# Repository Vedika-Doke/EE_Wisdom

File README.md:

# EE_Wisdom

**Engineering Projects & Research Repository**

Academic projects, hands-on engineering work, and interactive study tools spanning electrical engineering, embedded systems, digital design, and hardware development — built over multiple roles and coursework at IIT Bombay.

Each project lives in its own folder on `main`. Interactive study guides are served via GitHub Pages from the [`EE_LearningAids`](https://github.com/Vedika-Doke/EE_Wisdom/tree/EE_LearningAids) branch.

---

## Repository Structure

| Folder / Branch | Contents |
|---|---|
| [`WISH/`](WISH/) | TI WiSH Hardware Summer School (2026) — digital Verilog labs, analog prework/quizzes, and a smart bus-tracking group project (server-side ETA engine) |
| [`EE301-EMWaves/`](EE301-EMWaves/) | EE301 (Electromagnetic Waves) — full transmission-lines explainer, ground-floor-up |
| [`EE309-Microprocessors-Project/`](EE309-Microprocessors-Project/) | AT89C5131A + MCP4921 DAC + MCP3008 ADC — sine wave generation, NCO, Goertzel tone detection |
| [`EE337-MicroLab-Project/`](EE337-MicroLab-Project/) | 8051 MicroLab project — I2C LCD interfacing and R2C driver |
| [`Electrical-trainee-racing-team/`](Electrical-trainee-racing-team/) | ECU firmware, AMS/BMS research, HV-LV isolation, and comms protocol work for a student electric racing team |
| [`JDE-Tenure/`](JDE-Tenure/) | Two complete KiCad PCB designs — STM32 dashboard board and a sensor testing board |
| [`ToyCPU-1281/`](ToyCPU-1281/) | VHDL-based 8-bit toy CPU (i281) with custom ISA and Bubble Sort implementation |
| [`EE_LearningAids`](https://github.com/Vedika-Doke/EE_Wisdom/tree/EE_LearningAids) (branch) | Interactive browser-based study guides — [live site](https://vedika-doke.github.io/EE_Wisdom/) |

---

## EE_LearningAids

Interactive, single-file HTML study tools — open directly in any browser, no setup or internet needed.

### IIT Bombay Course Guides

#### EE238 — Power Engineering II
- 10 topic modules: transmission lines, 3-phase systems, per-unit analysis, ABCD parameters, P & Q flow, Maxwell's equations
- 18+ MCQs with click-to-reveal solutions
- 6 long-form worked problems (Review Q 5A style) with step-by-step strategies
- Textbook examples from Weedy Ch 2–3, master formula sheet
- Dark theme, mobile-friendly, works offline

#### EE309 — Microprocessors & Computer Architecture
- Full 8051 coverage: Von Neumann vs Harvard, memory map (ROM/RAM/SFR), internal RAM breakdown
- Registers, PSW flags, 5 addressing modes, instruction set (arithmetic, logical, jump, bit-level)
- Timers, interrupts (IE/IP registers, interrupt priority), serial communication (SCON, SBUF, baud rate)
- Machine cycles, timing diagrams, and common exam traps

### Aptitude & Test Prep (TI WiSH 2025)

#### `wish_prep.html` — TI WiSH Interactive Quiz
- Sections: Past Year Questions (WiSH 2024), Mathematics, Basic Electronics, Programming (tricky C)
- Full Mixed Mock Test mode (timed, randomized)
- Click-to-reveal explanations with worked solutions
- Covers: LTI systems, ROC, op-amps (CMRR, slew rate, virtual ground), MOSFET regions, CMOS, Boolean algebra, pointer arithmetic, short overflow, recursion output

#### `math_aptitude_mcq.html` — Advanced Math Bank
- 20 questions: Bayes' Theorem, Derangements, Pigeonhole Principle, Inclusion-Exclusion, Modular Arithmetic, Eigenvalues, Geometric Probability

#### `theory_revision.html` — Theory Revision Sheet
- **Probability:** Addition/Multiplication/Bayes rules, nPr/nCr, circular permutations, Stars & Bars, distributions (Binomial, Geometric, Poisson, Uniform), Expected Value, Variance, Derangements
- **Profit & Loss:** CP/SP/Profit%/Loss%, Mark-up + Discount formula, successive discounts, dishonest dealer, "sell x for cost of y" — with fraction↔percentage cheatsheet
- **C++ FAQs:** Data types & overflow, pointer arithmetic traps, operator precedence, bitwise tricks, storage classes, struct vs union vs class, virtual functions, time complexity table
- 45+ new interactive MCQs across all three topics with explanations

---

## Electrical-trainee-racing-team

Work done as an Electrical Trainee for a student FSAE electric racing team.

### `Comms/` — Controls, Communication & Data Acquisition

**ECU Firmware** (`Comms/Src/ECU/`) — C++ / PlatformIO
- FSAE rulebook-compliant ECU (Rules T11.8.x)
- CAN bus communication at 500 kbps; DBC file included for signal decoding
- APPS (Accelerator Pedal Position Sensor) plausibility check — 10% agreement threshold (T11.8.4)
- BPS (Brake Pressure Sensor) monitoring with hard-braking detection (T11.8.6)
- Torque command pipeline: APPS → scaled torque request → CAN frame to motor controller
- RFE acknowledgement sequencing, motor off-sequence with timed delays
- I2C/SPI/UART protocol implementations (PlatformIO project under `Comms/PlatformIO/`)

**Theory Notes** (`Comms/Theory/`)
- Serial vs parallel communication, simplex/half-duplex/full-duplex
- Deep dive into CAN, I2C, SPI, UART — framing, arbitration, addressing, error handling

### `AMS/` — Accumulator Management System

- BMS fundamentals: SOC (State of Charge), SOH (State of Health), SOE (State of Envelope)
- 96s5p Li-ion pack configuration (480 cells, max 403.2 V), stack architecture
- BMS protection: overvoltage, overcurrent, thermal cutoff
- `DataAnalysis.ipynb` — Python notebook for crude data analysis of accumulator telemetry
- PDF module notes: `AMS module '25.pdf`

### `HV_LV/` — High Voltage / Low Voltage Systems

- Galvanic isolation — theory and FSAE rulebook requirements (EV 1.2.1)
- Optocoupler interfacing (datasheet included)
- 555-timer theory notes
- ESI (Electronic System Integration) module notes — noise rejection, fault containment, ground loops

### `TheoryBits/` — Reference PDFs

Quick-reference theory sheets produced during the tenure:
- MOSFETs, Op-Amps & Phasors, Op-Amp 2.0, Buck Converter
- Communication Protocols, Digital Logic
- Team session notes (Racing Team April 4)

---

## JDE-Tenure

Two complete PCB designs, both fully designed in KiCad (schematic + layout + BOM + 3D model).

### `DASH_PCB_STM32/` — Dashboard PCB (STM32-based)

- STM32 microcontroller at the core
- Full KiCad project: schematic (`.kicad_sch`), PCB layout (`.kicad_pcb`), project file, net files, BOM (`.csv`), 3D model (`.step`)
- Multiple netlist iterations (`net.net` → `netfinal.net`) reflecting design revisions
- Design backups preserved (Nov 2025)

### `Sensor_testing_PCB/` — Sensor Testing Board

- Purpose-built board for validating sensor interfacing before integration
- Full KiCad project: schematic, PCB layout, BOM, net file
- Backup snapshots included (Sep 2025)

---

## ToyCPU-1281

Course project: design and implementation of an 8-bit toy CPU (i281).

- VHDL-based datapath and control unit
- Custom instruction set architecture (ISA)
- Bubble Sort implemented directly on memory data
- Functional simulation and verification

---

## WISH

TI **WiSH Hardware Mentee (2026)** — kept as an academic-help resource. See [`WISH/`](WISH/) for the full breakdown.

- **Week 1 — Digital Design:** two Verilog labs (shift-add and DFT-instrumented sequential multipliers) with testbenches, test plans, and simulation waveforms; prework guides and daily surveys
- **Week 2 — Analog:** prework, ASLKv2010 starter-kit reference, and topic quizzes (Fourier/Laplace, inductors, RC circuits)
- **Project — Smart Bus Tracking:** a rural bus tracking + ETA system with a runnable Python prediction engine (EWMA segment learning, dead reckoning, geofencing), full server-side math writeups, and design diagrams

---

## Tools & Technologies

| Category | Details |
|---|---|
| **Languages** | C++, Python, VHDL, HTML/JS |
| **Embedded** | PlatformIO, 8051, STM32, CAN bus |
| **PCB Design** | KiCad (schematic, layout, BOM, 3D) |
| **EDA / Simulation** | LTspice, Quartus, MATLAB/Simulink |
| **Protocols** | CAN (500 kbps), I2C, SPI, UART |
| **Domains** | Embedded systems, automotive electronics, digital design, power engineering, test prep tooling |

---

## EE309-Microprocessors-Project

Hardware project for EE309 (Microprocessors) — AT89C5131A microcontroller driving external DAC/ADC over SPI.

| Phase | Description |
|---|---|
| `phase1/` | Basic MCP4921 DAC sine wave output via lookup table |
| `phase2/` | NCO (Numerically Controlled Oscillator) — frequency-agile sine generation |
| `phase3/` | MCP3008 ADC integration — loopback DAC→ADC measurement |
| `phase3_goertzel/` | Goertzel algorithm for single-bin tone detection on ADC samples |
| `src/` | Latest working source files |

---

## Notes

- All HTML study tools are offline-capable — open in a browser or visit the [live site](https://vedika-doke.github.io/EE_Wisdom/).
- Study guides are served from the `EE_LearningAids` branch via GitHub Pages.

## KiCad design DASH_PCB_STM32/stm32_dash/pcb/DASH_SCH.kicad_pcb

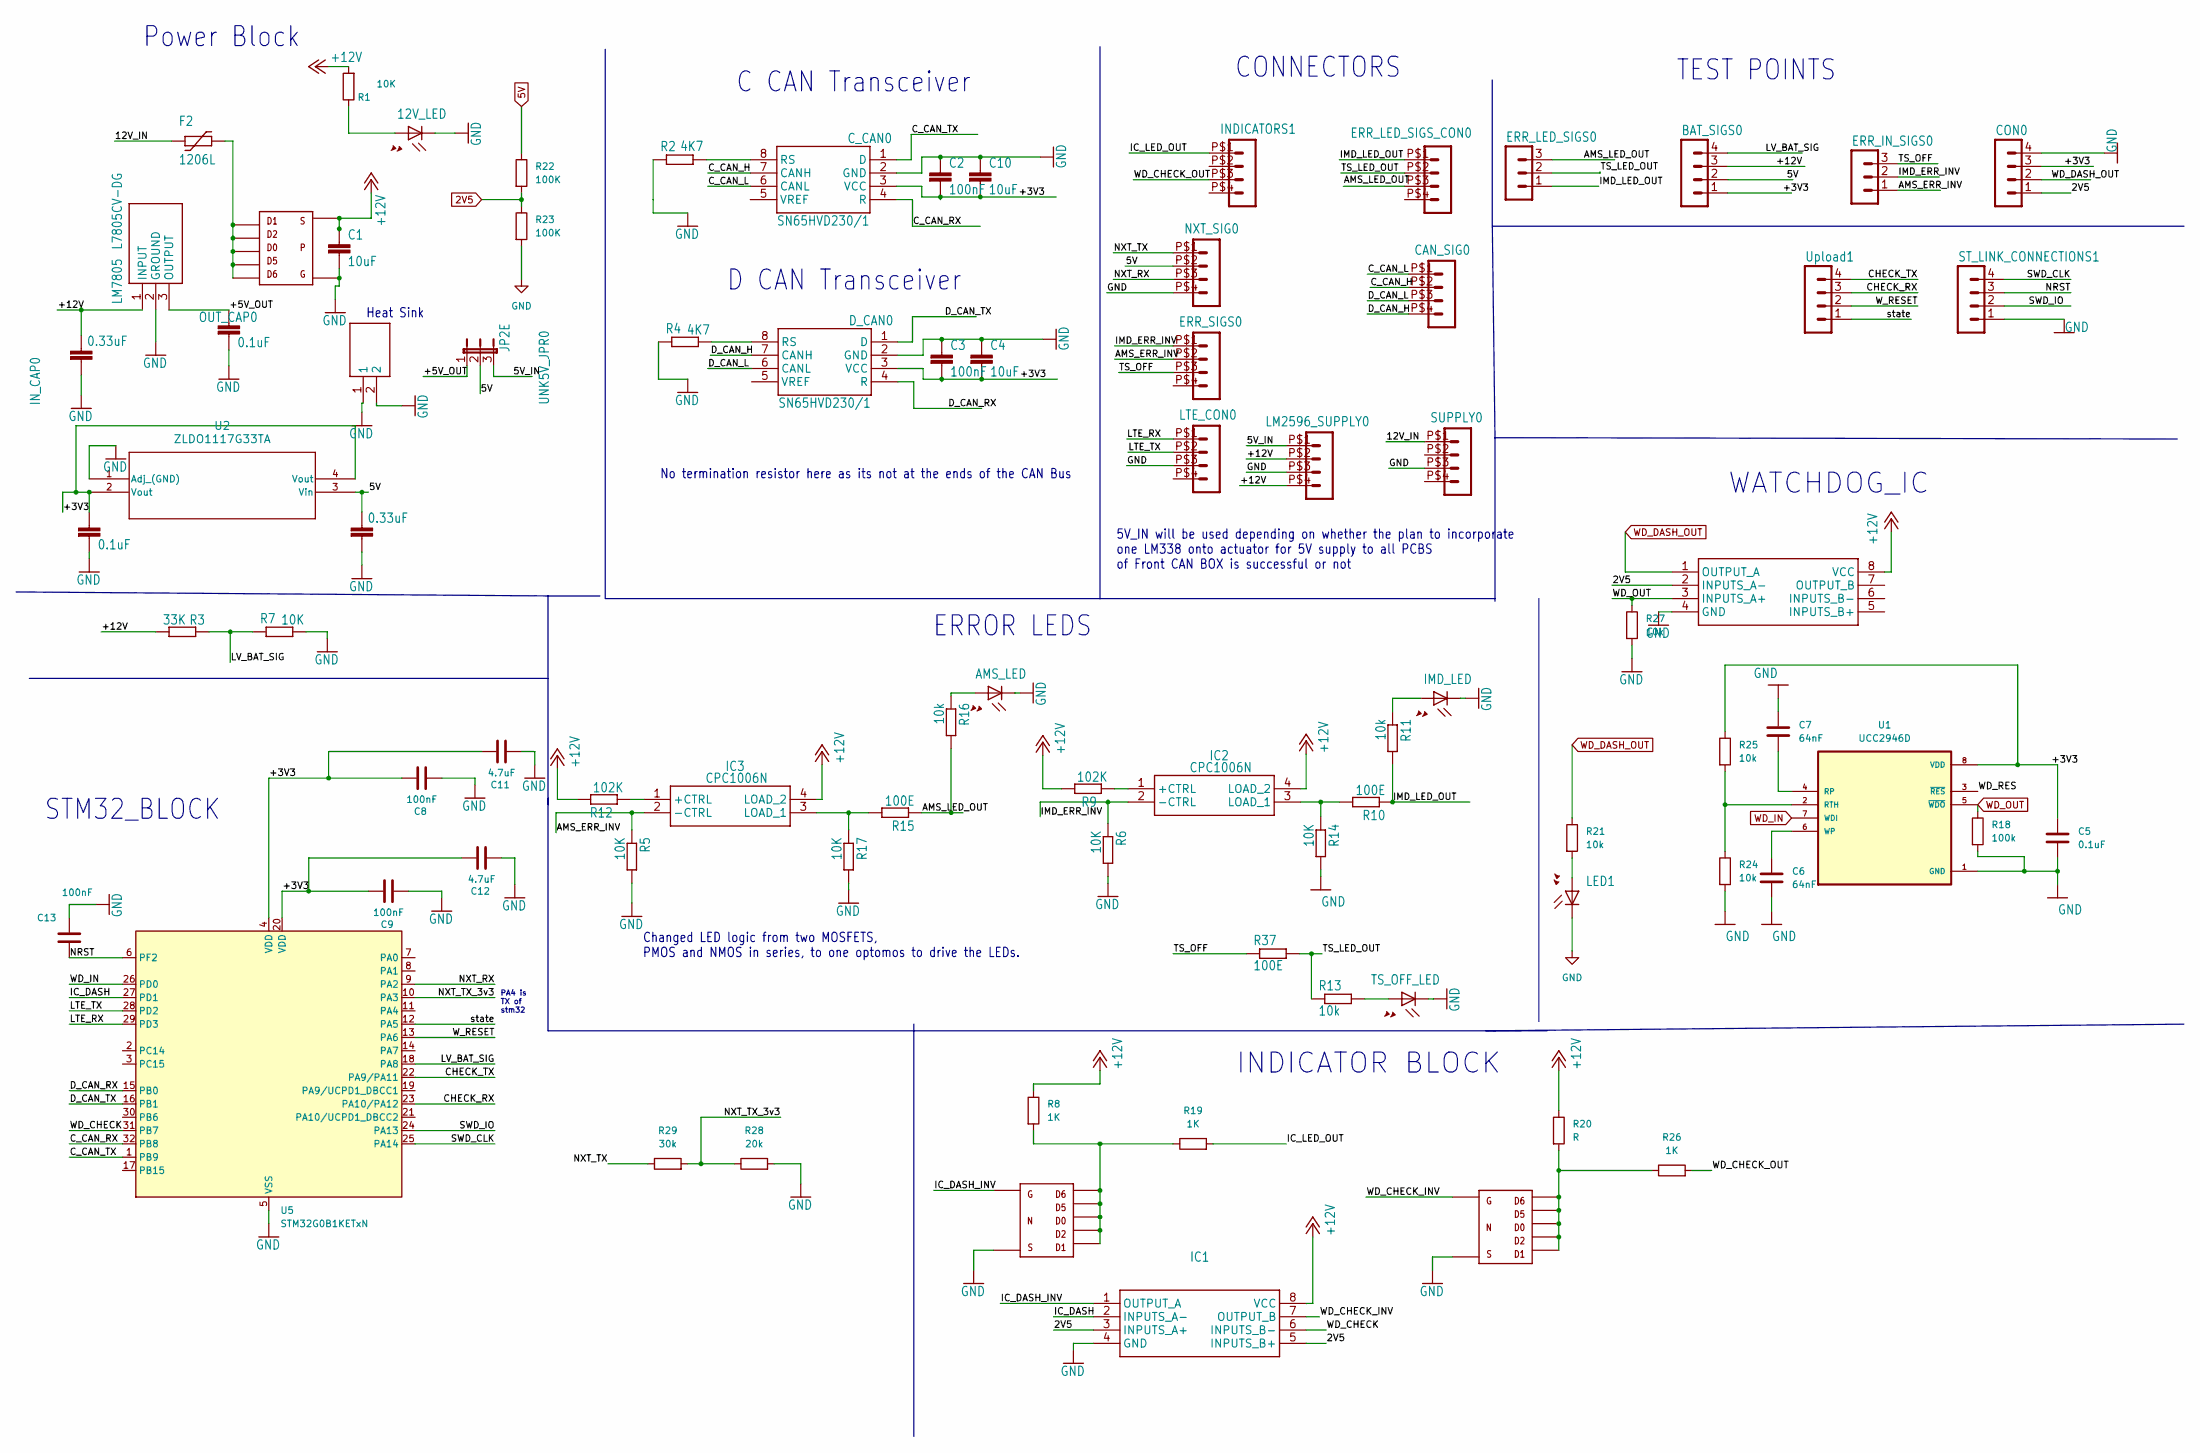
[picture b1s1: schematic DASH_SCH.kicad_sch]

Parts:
12V_LED1: 12V_LED; LED-1206
1111, 1211: TSOP-6_NMOS
AMS_LED0: AMS_LED; LED-1206
BAT_SIGS0: MA04-1_PINHEADERS; MA04-1
C1: 10uF; C_0805_2012Metric
C2, C3, C8, C9, C13: 100nF; C_0805_2012Metric_Pad1.18x1.45mm_HandSolder
C4, C10: 10uF; C_0805_2012Metric_Pad1.18x1.45mm_HandSolder
C5: 0.1uF; C_0805_2012Metric_Pad1.18x1.45mm_HandSolder
C6, C7: 64nF; C_0805_2012Metric_Pad1.18x1.45mm_HandSolder
C11, C12: 4.7uF; C_0805_2012Metric_Pad1.18x1.45mm_HandSolder
CAN_SIG0: HEADER_POS4_?43045-0412; 43045-0412
CON0: MA04-1_PINHEADERS; MA04-1
C_CAN0: SN65HVD230/1; SO8
D_CAN0: SN65HVD230/1; SO8
ERR_IN_SIGS0: MA03-1; MA03-1_162
ERR_LED_SIGS0: MA03-1; MA03-1_162
ERR_LED_SIGS_CON0: HEADER_POS4_?43045-0412; 43045-0412
ERR_SIGS0: HEADER_POS4_?43045-0412; 43045-0412
F2: 1206L
IC1, IC4: SOIC127P600X175-8N
IC2, IC3: CPC1006N; SOP254P610X216-4N
IMD_LED0: IMD_LED; LED-1206
INDICATORS1: HEADER_POS4_?43045-0412; 43045-0412
IN_CAP0, IN_CAP1: 0.33uF; C_0805_2012Metric_Pad1.18x1.45mm_HandSolder
LED1: LED-1206
LM2596_SUPPLY0: HEADER_POS4_?43045-0412; 43045-0412
LM7805: L7805CV-DG; TO255P460X1020X2008-3P
LTE_CON0: HEADER_POS4_?43045-0412; 43045-0412
NXT_SIG0: HEADER_POS4_?43045-0412; 43045-0412
OUT_CAP0, OUT_CAP1: 0.1uF; C0805
PMOS0: TSOP-6_PMOS
R1, R5, R6, R7, R14, R17: 10K; R_0805_2012Metric_Pad1.20x1.40mm_HandSolder
R2, R4: 4K7; R_0805_2012Metric_Pad1.20x1.40mm_HandSolder
R3: 33K; R_0805_2012Metric_Pad1.20x1.40mm_HandSolder
R8, R19, R26: 1K; R_0805_2012Metric_Pad1.20x1.40mm_HandSolder
R9, R12: 102K; R_0805_2012Metric_Pad1.20x1.40mm_HandSolder
R10, R15, R37: 100E; R_0805_2012Metric_Pad1.20x1.40mm_HandSolder
R11, R13, R16, R21, R24, R25, R27: 10k; R_0805_2012Metric_Pad1.20x1.40mm_HandSolder
R18: 100k; R_0805_2012Metric_Pad1.20x1.40mm_HandSolder
R20: R; R_0805_2012Metric_Pad1.20x1.40mm_HandSolder
R22, R23: 100K; R_0805_2012Metric_Pad1.20x1.40mm_HandSolder
R28: 20k; R_0805_2012Metric_Pad1.20x1.40mm_HandSolder
R29: 30k; R_0805_2012Metric_Pad1.20x1.40mm_HandSolder
ST_LINK_CONNECTIONS1: MA04-1_PINHEADERS; MA04-1
SUPPLY0: HEADER_POS4_?43045-0412; 43045-0412
TS_OFF_LED0: TS_OFF_LED; LED-1206
U1: UCC2946D; SOIC127P599X175-8N; DigiKey_Part_Number 296-2645-5-ND
U2: ZLDO1117G33TA; SOT230P700X185-4N
U3: HSS10-B20-P40; HSS10B20P40
U5: STM32G0B1KETxN; LQFP-32_7x7mm_P0.8mm
UNK5V_JPR0: JP2E; JP2_252
Upload1: MA04-1_PINHEADERS; MA04-1

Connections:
2V5: CON0.1, IC1.3 (INPUTS_A+), IC1.5 (INPUTS_B+), IC4.2 (INPUTS_A-), R22.2, R23.1
5V: BAT_SIGS0.2, IN_CAP1.1, NXT_SIG0.P$2 (2), R22.1, U2.3 (Vin), UNK5V_JPR0.2
+12V: BAT_SIGS0.3, C1.1, IC1.8 (VCC), IC2.4 (LOAD_2), IC3.4 (LOAD_2), IC4.8 (VCC), IN_CAP0.1, LM2596_SUPPLY0.P$2 (2), LM2596_SUPPLY0.P$4 (4), LM7805.1 (INPUT), PMOS0.S, R1.2, R3.1, R8.1, R9.2, R12.2, R20.1
/5V_IN: LM2596_SUPPLY0.P$1 (1), UNK5V_JPR0.3
/12V_IN: F2.P$1 (1), SUPPLY0.P$1 (1)
/+3V3: BAT_SIGS0.1, C2.2, C3.2, C4.2, C5.1, C8.1, C9.1, C10.2, C11.1, C12.1, CON0.3, C_CAN0.3 (VCC), D_CAN0.3 (VCC), OUT_CAP1.1, R25.1, U1.8 (VDD), U2.2 (Vout), U2.4 (Vout), U5.4 (VDD), U5.20 (VDD)
/+5V_OUT: LM7805.3 (OUTPUT), OUT_CAP0.1, UNK5V_JPR0.1
/AMS_ERR_INV: ERR_IN_SIGS0.1, ERR_SIGS0.P$2 (2), IC3.2 (-CTRL), R5.1
/AMS_LED_OUT: ERR_LED_SIGS0.3, R15.1, R16.2
/CHECK_RX: U5.23 (PA10/PA12), Upload1.3
/CHECK_TX: U5.22 (PA9/PA11), Upload1.4
/C_CAN_H: CAN_SIG0.P$2 (2), C_CAN0.7 (CANH)
/C_CAN_L: CAN_SIG0.P$1 (1), C_CAN0.6 (CANL)
/C_CAN_RX: C_CAN0.4 (R), U5.32 (PB8)
/C_CAN_TX: C_CAN0.1 (D), U5.1 (PB9)
/D_CAN_H: CAN_SIG0.P$4 (4), D_CAN0.7 (CANH)
/D_CAN_L: CAN_SIG0.P$3 (3), D_CAN0.6 (CANL)
/D_CAN_RX: D_CAN0.4 (R), U5.15 (PB0)
/D_CAN_TX: D_CAN0.1 (D), U5.16 (PB1)
/IC_DASH: IC1.2 (INPUTS_A-), U5.27 (PD1)
/IC_DASH_INV: 1111.G, IC1.1 (OUTPUT_A)
/IC_LED_OUT: INDICATORS1.P$1 (1), R19.2
/IMD_ERR_INV: ERR_IN_SIGS0.2, ERR_SIGS0.P$1 (1), IC2.2 (-CTRL), R6.1
/IMD_LED_OUT: ERR_LED_SIGS0.1, ERR_LED_SIGS_CON0.P$1 (1), R10.1, R11.2
/LTE_RX: LTE_CON0.P$1 (1), U5.29 (PD3)
/LTE_TX: LTE_CON0.P$2 (2), U5.28 (PD2)
/LV_BAT_SIG: BAT_SIGS0.4, R3.2, R7.1, U5.18 (PA8)
/NRST: C13.1, ST_LINK_CONNECTIONS1.3, U5.6 (PF2)
/NXT_RX: NXT_SIG0.P$3 (3), U5.9 (PA2)
/NXT_TX: NXT_SIG0.P$1 (1), R29.1
/NXT_TX_3v3: R28.1, R29.2, U5.10 (PA3)
/SWD_CLK: ST_LINK_CONNECTIONS1.4, U5.25 (PA14)
/SWD_IO: ST_LINK_CONNECTIONS1.2, U5.24 (PA13)
/TS_LED_OUT: ERR_LED_SIGS0.2, ERR_LED_SIGS_CON0.P$2 (2), R13.1, R37.2
/TS_OFF: ERR_IN_SIGS0.3, ERR_SIGS0.P$3 (3), R37.1
/WD_CHECK: IC1.6 (INPUTS_B-), U5.31 (PB7)
/WD_CHECK_INV: 1211.G, IC1.7 (OUTPUT_B)
/WD_CHECK_OUT: INDICATORS1.P$3 (3), R26.2
/WD_RES: U1.3 (~RES)
/W_RESET: U5.13 (PA6), Upload1.2
/state: U5.12 (PA5), Upload1.1
GND: 12V_LED1.C, 1111.S, 1211.S, AMS_LED0.C, C1.2, C2.1, C3.1, C4.1, C5.2, C6.2, C7.1, C8.2, C9.2, C10.1, C11.2, C12.2, C13.2, CON0.4, C_CAN0.2 (GND), D_CAN0.2 (GND), IC1.4 (GND), IC4.4 (GND), IMD_LED0.C, IN_CAP0.2, IN_CAP1.2, LED1.C, LM2596_SUPPLY0.P$3 (3), LM7805.2 (GROUND), LTE_CON0.P$3 (3), NXT_SIG0.P$4 (4), OUT_CAP0.2, OUT_CAP1.2, PMOS0.G, R2.1, R4.1, R5.2, R6.2, R7.2, R14.2, R17.2, R18.2, R23.2, R24.2, R27.2, R28.2, ST_LINK_CONNECTIONS1.1, SUPPLY0.P$3 (3), TS_OFF_LED0.C, U1.1 (GND), U2.1 (Adj_(GND)), U3.1, U3.2, U5.5 (VSS)
unnamed: 12V_LED1.A, R1.1
unnamed: 1111.1, 1111.2, 1111.5, 1111.6, 1111.D (D0), R8.2, R19.1
unnamed: 1211.1, 1211.2, 1211.5, 1211.6, 1211.D (D0), R20.2, R26.1
unnamed: AMS_LED0.A, R16.1
unnamed: C_CAN0.8 (RS), R2.2
unnamed: D_CAN0.8 (RS), R4.2
unnamed: F2.P$2 (2), PMOS0.1, PMOS0.2, PMOS0.5, PMOS0.6, PMOS0.D (D0)
unnamed: IC2.1 (+CTRL), R9.1
unnamed: IC2.3 (LOAD_1), R10.2, R14.1
unnamed: IC3.1 (+CTRL), R12.1
unnamed: IC3.3 (LOAD_1), R15.2, R17.1
unnamed: IMD_LED0.A, R11.1
unnamed: LED1.A, R21.2
unnamed: R13.2, TS_OFF_LED0.A
unnamed: C7.2, U1.4 (RP)
unnamed: R24.1, R25.2, U1.2 (RTH)
unnamed: C6.1, U1.6 (WP)
WD_DASH_OUT: CON0.2, IC4.1 (OUTPUT_A), R21.1
WD_IN: U1.7 (WDI), U5.26 (PD0)
WD_OUT: IC4.3 (INPUTS_A+), R18.1, R27.1, U1.5 (~WDO)

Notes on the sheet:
Power Block
No termination resistor here as its not at the ends of the CAN Bus
INDICATOR BLOCK
ERROR LEDS
C CAN Transceiver
CONNECTORS
Heat Sink
5V_IN will be used depending on whether the plan to incorporate one LM338 onto actuator for 5V supply to all PCBS of Front CAN BOX is successful or not
TEST POINTS
PA4 is TX of stm32
STM32_BLOCK
Changed LED logic from two MOSFETS, PMOS and NMOS in series, to one optomos to drive the LEDs.
D CAN Transceiver
WATCHDOG_IC

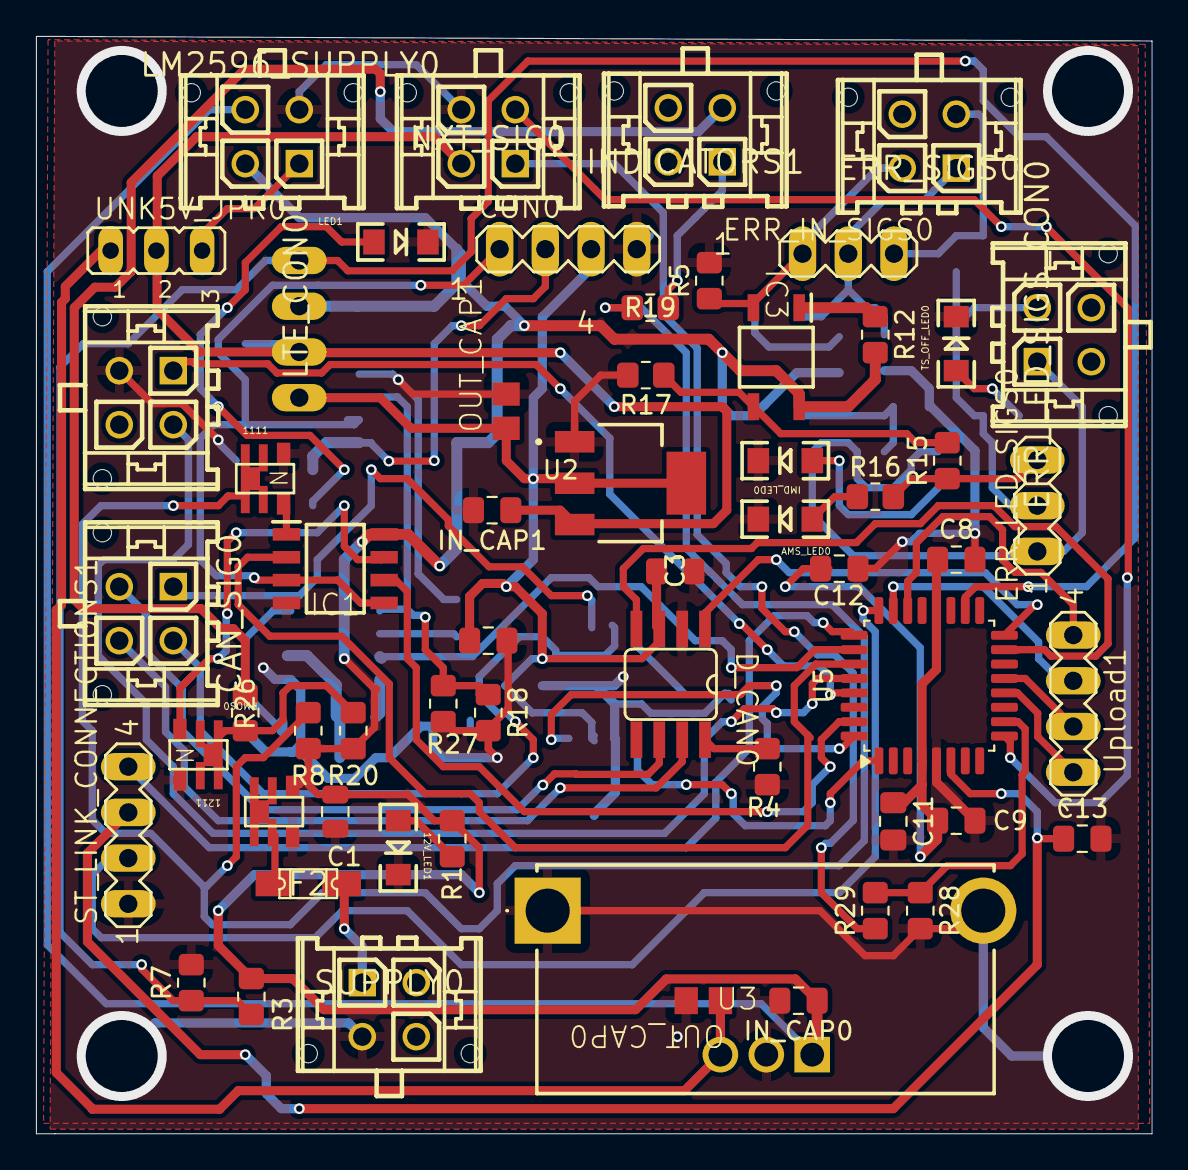
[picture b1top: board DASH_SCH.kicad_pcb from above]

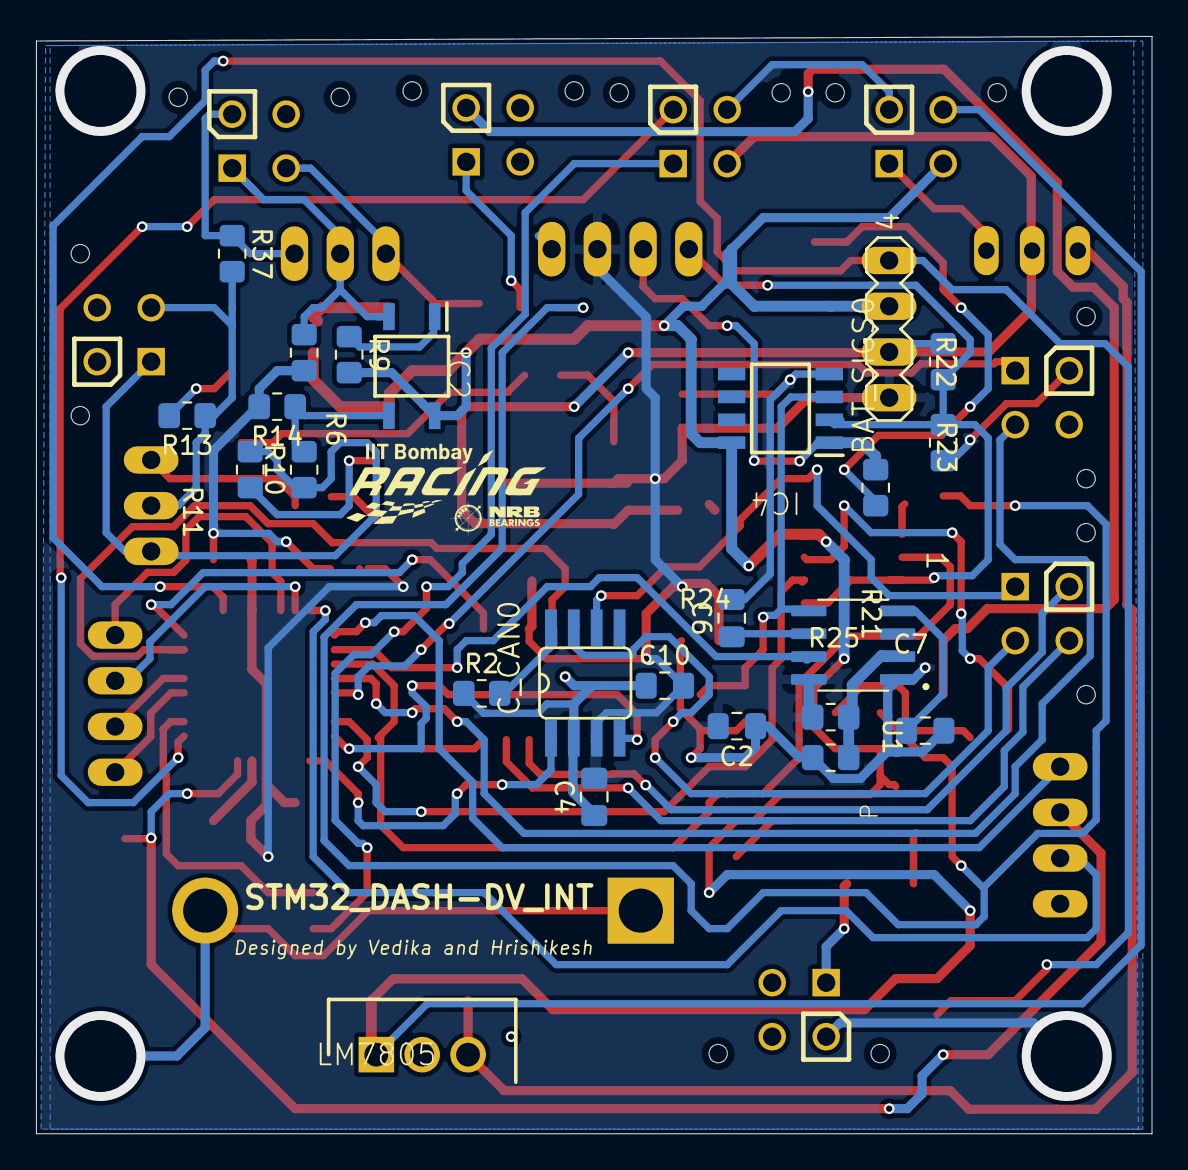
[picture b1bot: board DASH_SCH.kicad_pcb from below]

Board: 2 copper layers, 62.0 x 61.0 mm, 82 parts (24 on the bottom side), 61 nets.

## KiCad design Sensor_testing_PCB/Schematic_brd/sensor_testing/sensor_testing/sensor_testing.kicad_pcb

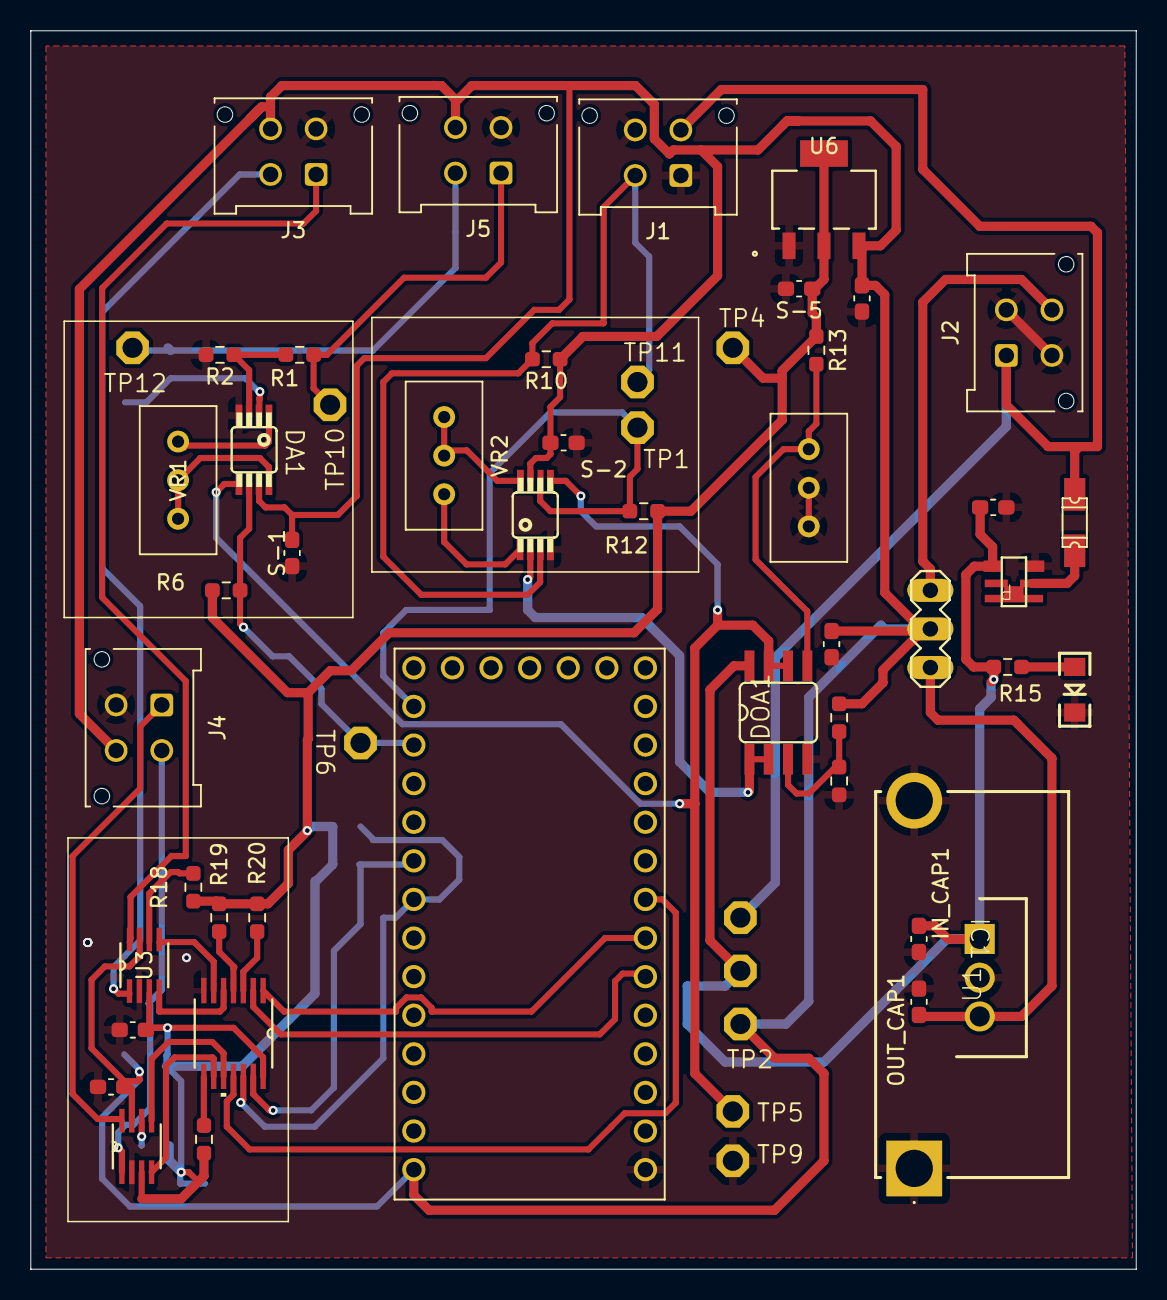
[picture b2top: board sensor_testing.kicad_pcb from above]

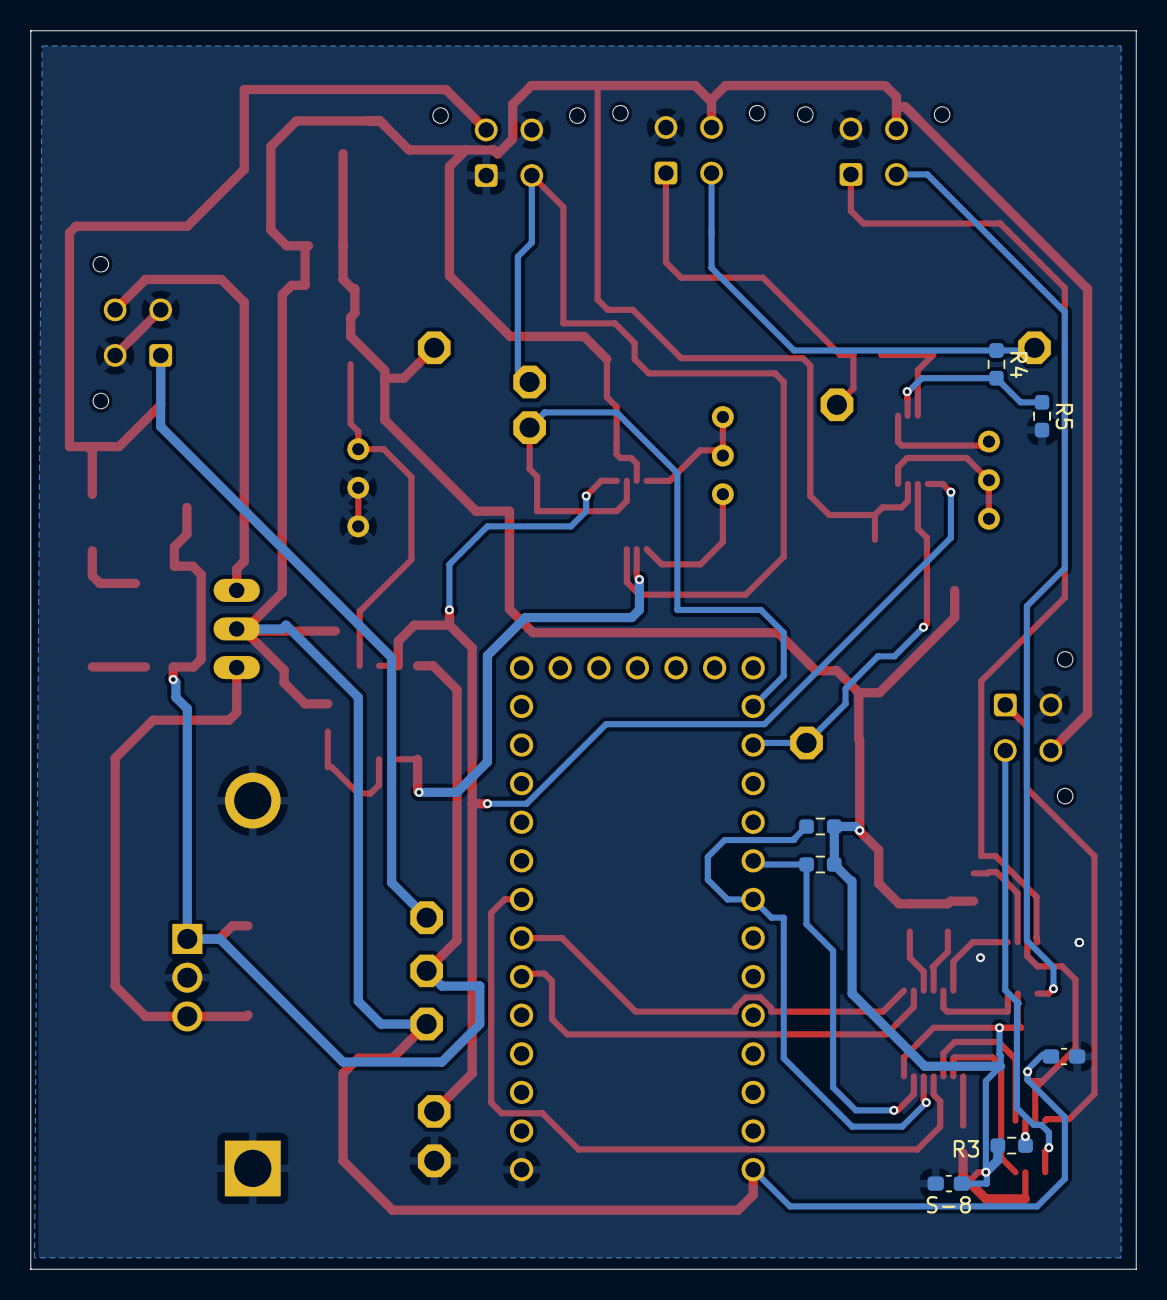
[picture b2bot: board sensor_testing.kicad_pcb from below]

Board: 2 copper layers, 72.8 x 81.5 mm, 63 parts (7 on the bottom side), 42 nets.

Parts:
C1: 10uF; C_0603_1608Metric_Pad1.08x0.95mm_HandSolder
DA1, DA2: INA333; MSOP8
DOA1: SO8
F1: 1206L
IC1: L7805CV-DG; TO255P460X1020X2008-3P
IN_CAP1: 0.33uF; C_0603_1608Metric_Pad1.08x0.95mm_HandSolder
J1, J2, J3, J4, J5: 430450412; Molex_Micro-Fit_3.0_43045-0412_2x02_P3.00mm_Vertical
OUT_CAP1: 0.1uF; C_0603_1608Metric_Pad1.08x0.95mm_HandSolder
R1, R4: 7k; R_0603_1608Metric_Pad0.98x0.95mm_HandSolder
R2, R5: 5k; R_0603_1608Metric_Pad0.98x0.95mm_HandSolder
R3, R6, R7, R8, R11, R12, R13, R15, R18, R19, R20: 10k; R_0603_1608Metric_Pad0.98x0.95mm_HandSolder
R10: 120; R_0603_1608Metric_Pad0.98x0.95mm_HandSolder
R16, R17: 10K; R_0603_1608Metric_Pad0.98x0.95mm_HandSolder
S-1, S-2, S-6, S-7, S-8, S-9: 0.1uF; C_0603_1608Metric_Pad1.08x0.95mm_HandSolder
S-3: 0.33uF; C_0603_1608Metric_Pad1.08x0.95mm_HandSolder
S-4: 1uF; C_0603_1608Metric_Pad1.08x0.95mm_HandSolder
S-5: 1nF; C_0603_1608Metric_Pad1.08x0.95mm_HandSolder
SV4: MA03-1; MA03-1_162
TP1, TP2, TP3, TP4, TP5, TP6, TP7, TP9, TP10, TP11, TP12: TPSQPAD1-13; P1-13_385
U1: HSS10-B20-P40; HSS10B20P40
U2: DEV-15583; MODULE_DEV-15583
U3, U5: TXS0102DCTR; DCT8
U4: TCA9543APWR; PW14
U6: ZLDO1117G33TA; SOT_G33TA_DIO
U$2: TSOP-6_PMOS
UNK12V_LED1: LED1206; LED-1206
VR1, VR2: 3296W-1-101LF; Potentiometer_Bourns_3296W_Vertical
VR3: 10k; Potentiometer_Bourns_3296W_Vertical

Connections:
+5V: DA1.7 (+V), DA2.7 (+V), J3.4, J4.4, J5.4, R8.1, R10.1, S-1.1, S-2.1, S-3.1, S-4.1, S-7.2, S-9.2, SV4.2, TP2.TP, U2.VIN, U3.7 (VCCB), U5.7 (VCCB), U6.3 (Vin)
+12V: C1.1, DOA1.8 (V+), IC1.1 (INPUT), IN_CAP1.1, R15.2, TP7.TP, U$2.S
/1.65V_REF: DA1.5 (REF), DA2.5 (REF), DOA1.6 (-IN), DOA1.7 (OUT), TP5.TP
/5V_IN: J2.4, SV4.3
/5V_OUT: IC1.3 (OUTPUT), OUT_CAP1.1, SV4.1
/12V_IN: F1.P$1 (1), J1.3, J2.1, TP3.TP
/+2.5V: DA2.2 (-), DOA1.1 (OUT), DOA1.2 (-IN)
/+3V3: R3.1, R6.1, R7.1, R12.1, R13.1, R16.1, R17.1, R18.1, R19.1, R20.1, S-5.1, S-6.1, S-8.1, TP4.TP, U3.3 (VCCA), U4.14 (VCC), U5.3 (VCCA), U6.2 (Vout), U6.4 (Vout)
/A0: U2.5, U4.1 (AO)
/A1: U2.4, U4.2 (A1)
/INT: U2.6, U4.11 (INT)
/LOAD_CELL_DIV1+: DA1.3 (+), R1.2, R2.1
/LOAD_CELL_DIV1-: DA1.2 (-), R4.2, R5.1
/LOAD_CELL_FR+: J5.1, R1.1, TP10.TP
/LOAD_CELL_FR-: J5.2, R4.1, TP12.TP
/LOAD_CELL_FR_IN: DA1.6 (OUT), R6.2, TP6.TP, U2.15
/R+SG_FR: DA1.8 (RG@1), VR1.2, VR1.3
/R+SG_S2: DA2.8 (RG@1), VR2.2, VR2.3
/R-SG_FR: DA1.1 (RG), VR1.1
/R-SG_S2: DA2.1 (RG), VR2.1
/SCL0_3V3: U3.5 (A1), U4.6 (SCO)
/SCL1_3V3: U4.10 (8C1), U5.5 (A1)
/SCL_3V3: R17.2, U2.19, U4.12 (SCL)
/SDA0_3V3: U3.4 (A2), U4.5 (SDO)
/SDA1_3V3: U4.9 (SD1), U5.4 (A2)
/SDA_3V3: R16.2, U2.18, U4.13 (SDA)
/SENS0_SCL: J3.1, U3.8 (B1)
/SENS0_SDA: J3.2, U3.1 (B2)
/SENS1_SCL: J4.1, U5.8 (B1)
/SENS1_SDA: J4.2, U5.1 (B2)
/STRAIN_FR_2+: DA2.3 (+), J1.2, R10.2, TP11.TP
/STRAIN_GAUGE_FR2_IN: DA2.6 (OUT), R12.2, TP1.TP, U2.14
GND: C1.2, DA1.4 (-V), DA2.4 (-V), DOA1.4 (V-), IC1.2 (GROUND), IN_CAP1.2, J1.1, J1.4, J2.2, J2.3, J3.3, J4.3, J5.3, OUT_CAP1.2, R2.2, R5.2, R11.2, S-1.2, S-2.2, S-3.2, S-4.2, S-5.2, S-6.2, S-7.1, S-8.2, S-9.1, TP9.TP, U1.1, U1.2, U2.G1, U3.2 (GND), U4.7 (GND), U5.2 (GND), U6.1 (Adj_(GND)), U$2.G, UNK12V_LED1.C, VR3.2, VR3.3
unnamed: DOA1.3 (+IN), R8.2, R11.1
unnamed: DOA1.5 (+IN), R13.2, VR3.1
unnamed: F1.P$2 (2), U$2.1, U$2.2, U$2.5, U$2.6, U$2.D (D0)
unnamed: R15.1, UNK12V_LED1.A
unnamed: R18.2, U3.6 (OE)
unnamed: R7.2, U4.8 (INT1)
unnamed: R19.2, U4.4 (INTO)
unnamed: R20.2, U4.3 (RESET)
unnamed: R3.2, U5.6 (OE)

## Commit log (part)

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2025-06-15 Comms
2025-06-15 Notes
2025-06-15 cleanup
2025-06-16 HvLv
2025-06-25 Rename HVLV_Vedika_24b1231.md to 555-timer_Vedika_24b1231.md
2026-01-31 Sensor_test
2026-01-31 DASH
2026-01-31 Enhance README with project and tool information
    Expanded the README to include project descriptions, tools, and organization details.
2026-01-31 Refactor 'pcb-design-projects' section in README
    Updated the formatting and structure of the 'pcb-design-projects' section in README.md.
2026-03-24 Add EE238 Power Engineering II ultimate study guide
    Complete HTML study guide covering transmission lines, 3-phase systems,
    per-unit, ABCD matrices, P&Q flow, Maxwell's equations, and more.
    Includes 18+ MCQs with solutions, 6 long problems, worked textbook
    examples from Weedy Ch 2-3, and a master formula sheet.
2026-03-24 Improve study guide: better explanations, diagrams, formatting fixes
    - Fix equation formatting (use div elements instead of pre-wrap)
    - Fix SVG diagrams (power transfer, bundled conductor Q3)
    - Add detailed explanations for Q6 (X/R ratio), Q7 (line data), Q16 (Ferranti)
    - Add voltage profile bowl-shape diagram for Q16
    - Add corona, ground wire, TEM voltage paradox, mutual coupling sections
    - Add OTL vs cable comparison table
2026-03-25 Add Q25-Q32: new MCQ from Weedy textbook content
2026-03-25 Add EE309 Microprocessors & Computer Architecture study guide
    Complete interactive HTML study guide covering 8051 microcontroller
    (architecture, memory, registers, addressing, instructions, timers,
    interrupts, serial communication, multiprocessor), MIPS ISA, datapath
    (single-cycle & multi-cycle), pipelining, cache memory, and computer
    architecture performance/power concepts with SVG visualizations.
2026-03-25 Fix V_dd tradeoff SVG: correct Power/Delay/EDP curves with optimal voltage marker
2026-03-25 Add detailed R-type instruction breakdown with binary encoding example
2026-03-25 Expand I-Type and J-Type with extension table, binary examples, address formation
2026-03-25 Add comprehensive instruction reference & interactive quiz
    - Added Section 5B: Complete 8051 instruction reference with all 111
    instructions, full forms, syntax, operations, bytes, MCs, and flags
    - Covers Arithmetic, Logical, Data Transfer, Boolean/Bit, and Branching
    - Added quick-reference card for all mnemonics and their full forms
    - Added addressing mode notation guide
    - Added interactive quiz with 50+ MCQs covering 8051 & MIPS topics
2026-03-25 Add detailed plain-English explanations for multi-cycle datapath
    - Added "In plain English" explanations for each of the 5 cycles
    - Added notation decoder table (IR, X, Y, Z, MDR, bit fields)
    - Added "Why this many cycles?" column to CPI table
    - Explained why lw is the slowest instruction (5 cycles)
2026-03-25 Add MIPS instruction ref, datapath simulator, MMU/VM section, and more
    - Complete MIPS instruction reference with full forms (arithmetic,
    logical, shift, memory, branch/jump, special + pseudo instructions)
    - Interactive single-cycle datapath simulator with control signals
    - Split-cycle register file explanation for data hazards
    - Multi-cycle datapath detailed plain-English explanations
    - ISA classification table with advantages/disadvantages
2026-03-25 Add detailed datapath component explanations and lw/sw examples
    - ALU-to-memory constraint: ALU result goes as address only, never data
    - Step-by-step lw/sw examples showing data flow through datapath
    - Instruction field routing table (opcode, rs, rt, rd, imm, funct)
    - All 4 MUXes explained (RegDst, ALUSrc, MemToReg, PCSrc)
    - ALU Control unit with ALUOp + funct field decoding table
    - Two adders (PC+4, Branch) and Shift Left 2 explained
2026-03-26 Fix mobile responsiveness: scrollable nav/tables, proper sizing
2026-03-26 Add no-cache meta headers to prevent stale previews
2026-03-26 Replace EE309_Study_Guide with complete version including Power & EDP
2026-03-28 Add Power & EDP practice problems section with 6 solved problems
    Covers DVFS optimization, static+dynamic power, parallel execution,
    pipelining EDP, voltage selection, and power gating — matching
    Tutorial 3 and exam-style question formats.
2026-03-29 Update README to reflect all branch contents
2026-03-29 Fix T5 MOSFET I_D answer: 40 mA not 20 mA (½ was double-applied)
2026-03-29 Remove SNU ISP 2026 guide
2026-04-03 Add CPI practice problems, cache details, pipeline tutorial traces, J-type example, sign-extension examples
    - Added Ideal CPI=1 explanation, actual CPI formula with stalls
    - Added 6 CPI practice problems with collapsible solutions (load-use, branch, forwarding, prediction)
    - Added Three Cs of cache misses, multilevel AMAT formula, SRAM vs DRAM comparison, 6 cache optimizations
    - Added Amdahl's Law worked examples from textbook (web server, FSQRT)
    - Added J-type instruction encoding/decoding worked example
    - Added addi vs ori sign-extension worked examples (0x8000, lui+ori vs lui+addi)
2026-04-03 Expand pseudo-instructions section with complete decomposition tables
    - Organized into 4 tables: Data Movement, Arithmetic/Logic, Branch, Set-on-condition
    - Added unsigned branch pseudos (bltu, bleu, bgtu, bgeu)
    - Added beqz, bnez, subi, negu, seq, sne, sge, sgt, sle
    - Each entry shows exact real instruction decomposition with logic explanation
    - Fixed pipeline tutorial Part (a) i4 stall labels from SH to DH, i5 SH reason
    - Fixed Part (b): i3 and i5 pass stalling instructions (no dependency)
2026-04-10 Fix time period condition in Monostable Multivibrator
    Corrected the description of the time period between trigger signals in the Monostable Multivibrator section.
2026-04-12 Add EE309 Intermodulation Distortion Project Guide
2026-04-12 Expand tone measurement section with detailed explanations and pseudocode
2026-04-14 Reorganize repo: move branch content into folders on main
    Migrate Electrical-trainee-racing-team, JDE-Tenure, and ToyCPU-1281
    branches into folders on main. Add EE309-Microprocessors-Project with
    all phase folders. EE_LearningAids branch kept alive for GitHub Pages.
2026-04-14 Add EE337 MicroLab Course Project - Phase 3
2026-06-17 Add WISH bus tracking simulator (single-file HTML demo)
2026-06-18 Drop '(Person 2)' from page title
2026-06-18 wish
